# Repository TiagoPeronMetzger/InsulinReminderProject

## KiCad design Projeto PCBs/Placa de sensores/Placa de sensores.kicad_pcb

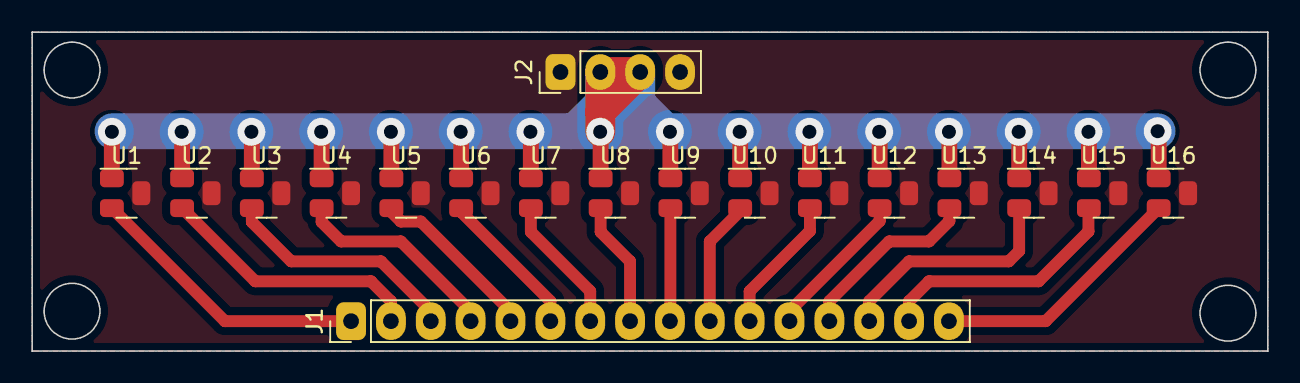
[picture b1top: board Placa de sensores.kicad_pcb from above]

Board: 2 copper layers, 78.7 x 20.3 mm, 18 parts (0 on the bottom side), 18 nets.

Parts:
J1: Conn_01x16_MountingPin; PinHeader_1x16_P2.54mm_Vertical
J2: Conn_01x04; PinHeader_1x04_P2.54mm_Vertical
U1, U2, U3, U4, U5, U6, U7, U8, U9, U10, U11, U12, U13, U14, U15, U16: 49E; SOT-23

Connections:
+5V: J2.2, J2.3, U1.1 (VCC), U2.1 (VCC), U3.1 (VCC), U4.1 (VCC), U5.1 (VCC), U6.1 (VCC), U7.1 (VCC), U8.1 (VCC), U9.1 (VCC), U10.1 (VCC), U11.1 (VCC), U12.1 (VCC), U13.1 (VCC), U14.1 (VCC), U15.1 (VCC), U16.1 (VCC)
/s1: J1.1, U1.2 (OUT)
/s2: J1.2, U2.2 (OUT)
/s3: J1.3, U3.2 (OUT)
/s4: J1.4, U4.2 (OUT)
/s5: J1.5, U5.2 (OUT)
/s6: J1.6, U6.2 (OUT)
/s7: J1.7, U7.2 (OUT)
/s8: J1.8, U8.2 (OUT)
/s9: J1.9, U9.2 (OUT)
/s10: J1.10, U10.2 (OUT)
/s11: J1.11, U11.2 (OUT)
/s12: J1.12, U12.2 (OUT)
/s13: J1.13, U13.2 (OUT)
/s14: J1.14, U14.2 (OUT)
/s15: J1.15, U15.2 (OUT)
/s16: J1.16, U16.2 (OUT)
GND: J2.1, J2.4, U1.3 (GND), U2.3 (GND), U3.3 (GND), U4.3 (GND), U5.3 (GND), U6.3 (GND), U7.3 (GND), U8.3 (GND), U9.3 (GND), U10.3 (GND), U11.3 (GND), U12.3 (GND), U13.3 (GND), U14.3 (GND), U15.3 (GND), U16.3 (GND)

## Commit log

2022-08-15 add project
2022-09-07 PCB Sensores
